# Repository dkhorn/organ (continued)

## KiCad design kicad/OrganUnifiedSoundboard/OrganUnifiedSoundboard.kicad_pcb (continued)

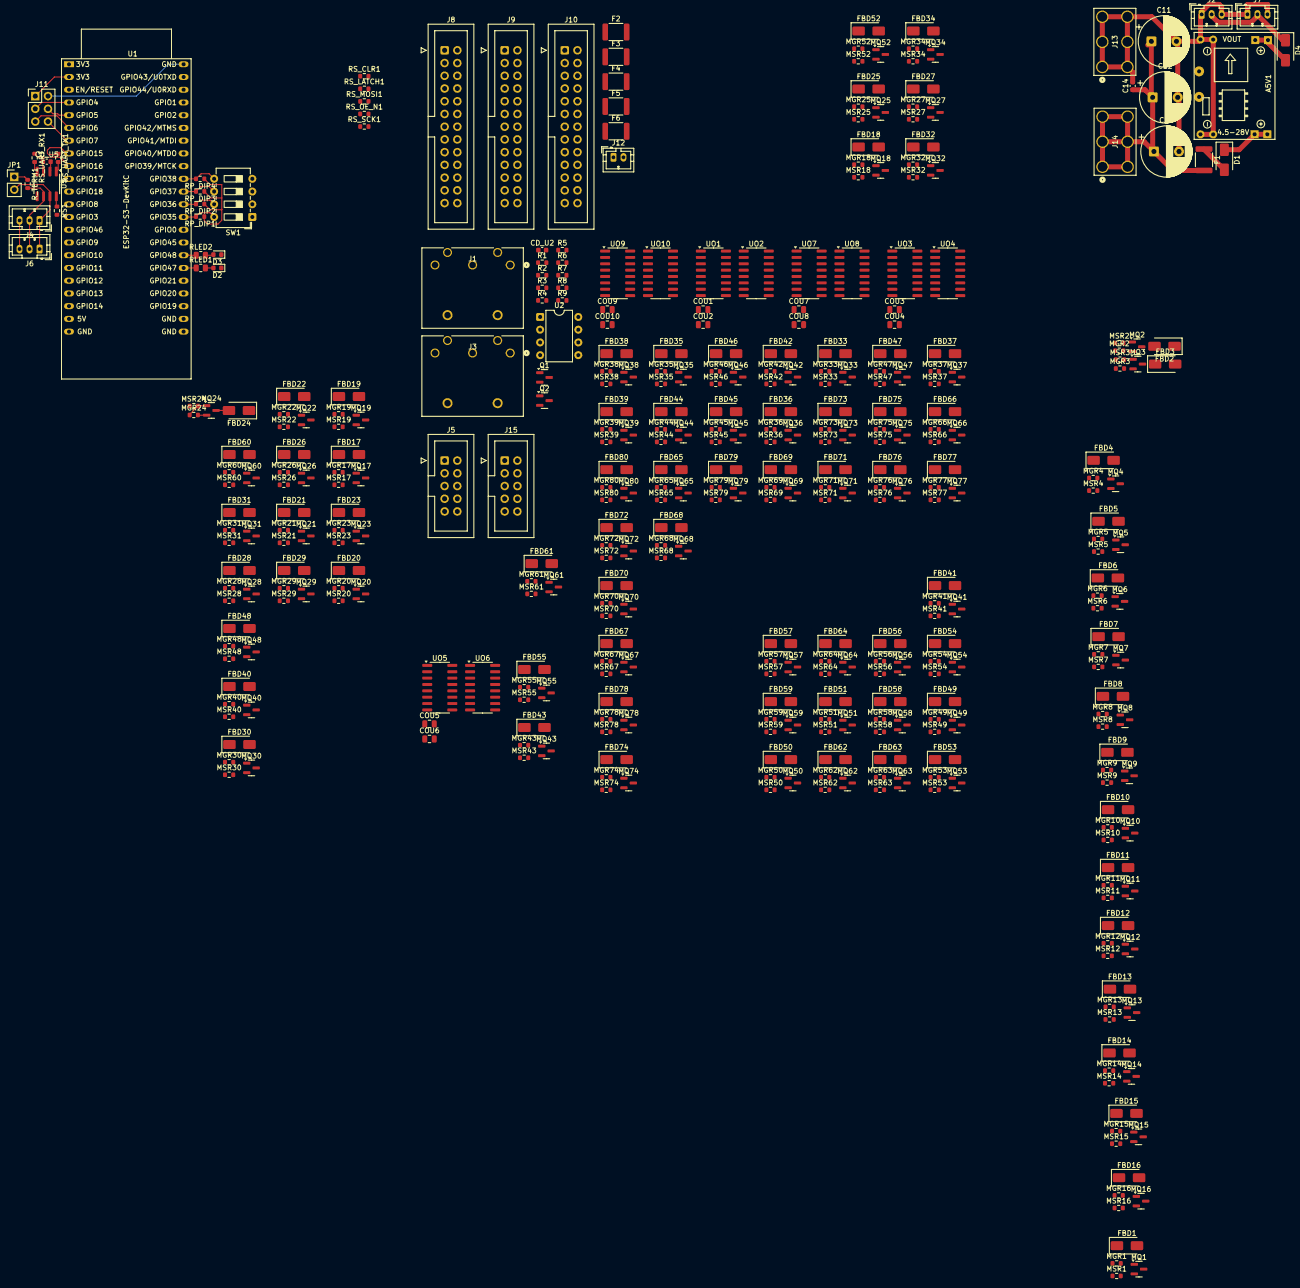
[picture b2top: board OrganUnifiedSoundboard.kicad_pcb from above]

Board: 2 copper layers, 403 parts (0 on the bottom side), 303 nets.

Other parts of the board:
J4: CAN_THRU; JST_PH_B3B-PH-K_1x03_P2.00mm_Vertical

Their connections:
/Controller/BoardToBoardComms/CANH: J4.1; also elsewhere on the board
/Controller/BoardToBoardComms/CANL: J4.2; also elsewhere on the board
GND: J4.3; also elsewhere on the board

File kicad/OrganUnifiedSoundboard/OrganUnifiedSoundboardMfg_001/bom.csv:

Designator,Footprint,Quantity,Value,LCSC Part #
"C11, C12, C13",CP_Radial_D10.0mm_P5.00mm,3,2200u 25V,
"C14, CD_U2, CD_U5",0603,3,100n,
"COU1, COU10, COU2, COU3, COU4, COU5, COU6, COU7, COU8, COU9",0805,10,0.1u,
CR1,SMCJSeries_LTF,1,SMCJ24A,
"D2, D3",0603,2,LED,
D4,D_SMA,1,SS14,
J10,IDC-Header_2x13_P2.54mm_Vertical,1,Outputs 53-78,
J8,IDC-Header_2x13_P2.54mm_Vertical,1,Outputs 1-26,
J9,IDC-Header_2x13_P2.54mm_Vertical,1,Outputs 27-52,
"MGR1, MGR10, MGR11, MGR12, MGR13, MGR14, MGR15, MGR16, MGR17, MGR18, MGR19, MGR2, MGR20, MGR21, MGR22, MGR23, MGR24, MGR25, MGR26, MGR27, MGR28, MGR29, MGR3, MGR30, MGR31, MGR32, MGR33, MGR34, MGR35, MGR36, MGR37, MGR38, MGR39, MGR4, MGR40, MGR41, MGR42, MGR43, MGR44, MGR45, MGR46, MGR47, MGR48, MGR49, MGR5, MGR50, MGR51, MGR52, MGR53, MGR54, MGR55, MGR56, MGR57, MGR58, MGR59, MGR6, MGR60, MGR61, MGR62, MGR63, MGR64, MGR65, MGR66, MGR67, MGR68, MGR69, MGR7, MGR70, MGR71, MGR72, MGR73, MGR74, MGR75, MGR76, MGR77, MGR78, MGR79, MGR8, MGR80, MGR9, R4, R9",0603,82,100K,
"MQ1, MQ10, MQ11, MQ12, MQ13, MQ14, MQ15, MQ16, MQ17, MQ18, MQ19, MQ2, MQ20, MQ21, MQ22, MQ23, MQ24, MQ25, MQ26, MQ27, MQ28, MQ29, MQ3, MQ30, MQ31, MQ32, MQ33, MQ34, MQ35, MQ36, MQ37, MQ38, MQ39, MQ4, MQ40, MQ41, MQ42, MQ43, MQ44, MQ45, MQ46, MQ47, MQ48, MQ49, MQ5, MQ50, MQ51, MQ52, MQ53, MQ54, MQ55, MQ56, MQ57, MQ58, MQ59, MQ6, MQ60, MQ61, MQ62, MQ63, MQ64, MQ65, MQ66, MQ67, MQ68, MQ69, MQ7, MQ70, MQ71, MQ72, MQ73, MQ74, MQ75, MQ76, MQ77, MQ78, MQ79, MQ8, MQ80, MQ9",SOT-23,80,Si2308CDS-T1-GE3,
"MSR1, MSR10, MSR11, MSR12, MSR13, MSR14, MSR15, MSR16, MSR17, MSR18, MSR19, MSR2, MSR20, MSR21, MSR22, MSR23, MSR24, MSR25, MSR26, MSR27, MSR28, MSR29, MSR3, MSR30, MSR31, MSR32, MSR33, MSR34, MSR35, MSR36, MSR37, MSR38, MSR39, MSR4, MSR40, MSR41, MSR42, MSR43, MSR44, MSR45, MSR46, MSR47, MSR48, MSR49, MSR5, MSR50, MSR51, MSR52, MSR53, MSR54, MSR55, MSR56, MSR57, MSR58, MSR59, MSR6, MSR60, MSR61, MSR62, MSR63, MSR64, MSR65, MSR66, MSR67, MSR68, MSR69, MSR7, MSR70, MSR71, MSR72, MSR73, MSR74, MSR75, MSR76, MSR77, MSR78, MSR79, MSR8, MSR80, MSR9",0603,80,100R,
"Q1, Q2",SOT-23,2,MMBT3904,
"R1, R8, RP_DIP1, RP_DIP2, RP_DIP3, RP_DIP4, RS1",0603,7,10k,
"R2, R5, R7",0603,3,220R,
R3,0603,1,2.2K,
R6,0603,1,4.7k,
"RLED1, RLED2",0805,2,4.7k,
"RS_UART_RX1, RS_UART_TX1",0603,2,33R,
R_TERM1,0603,1,120R,
U2,DIP-8_W7.62mm,1,6N137,
U5,SOIC-8_3.9x4.9mm_P1.27mm,1,SN65HVD230,
"UO1, UO10, UO2, UO3, UO4, UO5, UO6, UO7, UO8, UO9",SOP-16_3.9x9.9mm_P1.27mm,10,74HC595,

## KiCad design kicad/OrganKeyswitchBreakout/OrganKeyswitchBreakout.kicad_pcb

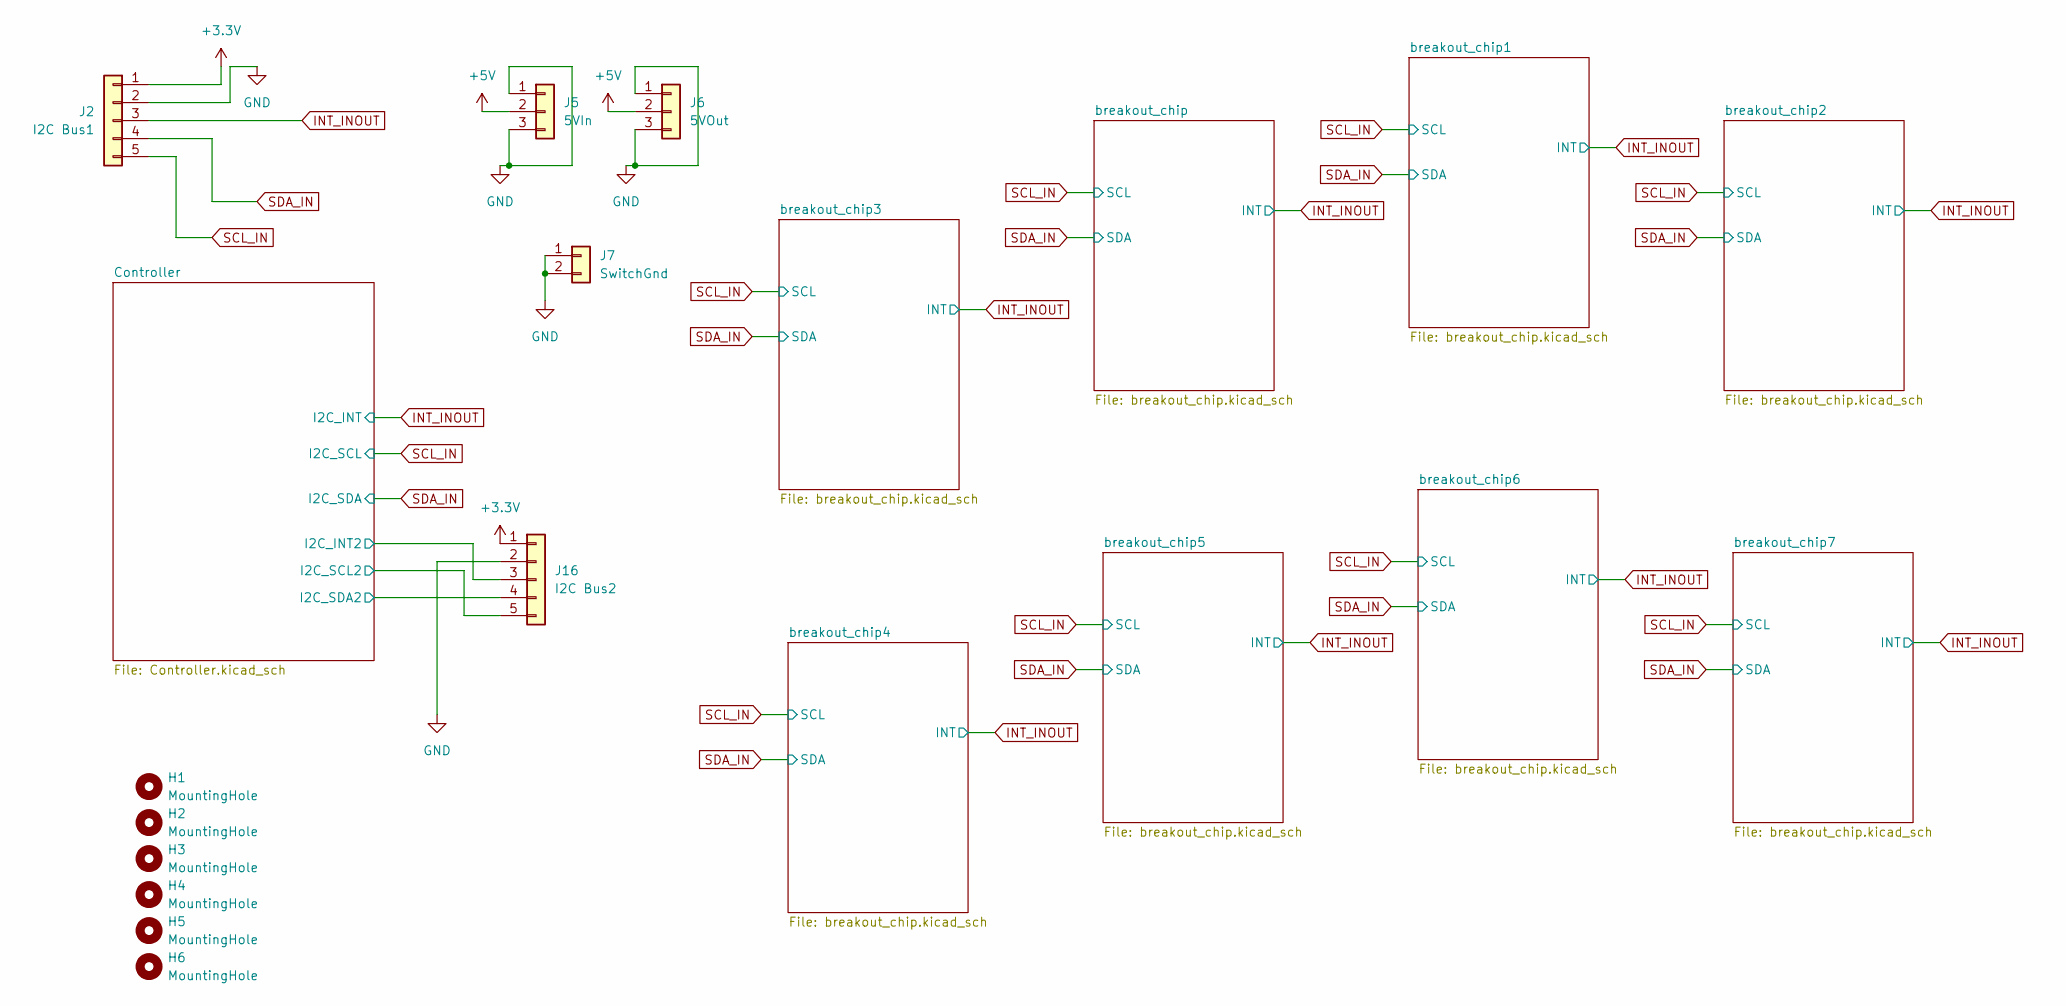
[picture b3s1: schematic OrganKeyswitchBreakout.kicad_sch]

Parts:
H1, H2, H3, H4, H5, H6: MountingHole; MountingHole_3.2mm_M3
J2: I2C Bus1; JST_PH_B5B-PH-K_1x05_P2.00mm_Vertical
J5: 5VIn; JST_PH_B3B-PH-K_1x03_P2.00mm_Vertical
J6: 5VOut; JST_PH_B3B-PH-K_1x03_P2.00mm_Vertical
J7: SwitchGnd; JST_PH_B2B-PH-K_1x02_P2.00mm_Vertical
J16: I2C Bus2; JST_PH_B5B-PH-K_1x05_P2.00mm_Vertical

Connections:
+3.3V: J2.1, J16.1; also elsewhere on the board
+5V: J5.2, J6.2; also elsewhere on the board
/Controller/I2C_INT2: J16.3; also elsewhere on the board
/Controller/I2C_SCL2: J16.5; also elsewhere on the board
/Controller/I2C_SDA2: J16.4; also elsewhere on the board
GND: J2.2, J5.1, J5.3, J6.1, J6.3, J7.1, J7.2, J16.2; also elsewhere on the board
INT_INOUT: J2.3; also elsewhere on the board
SCL_IN: J2.5; also elsewhere on the board
SDA_IN: J2.4; also elsewhere on the board

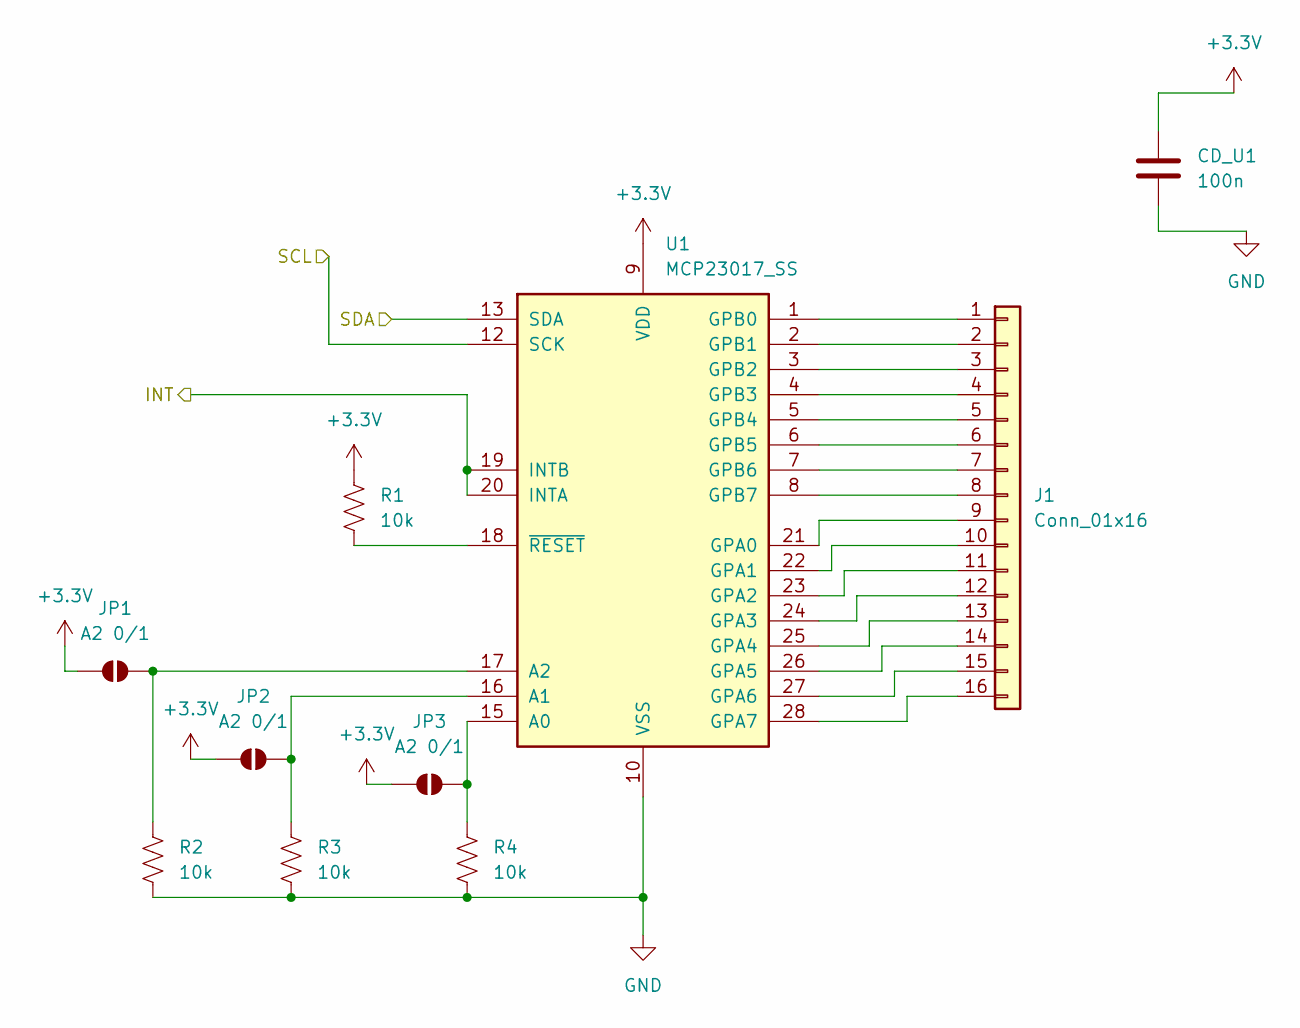
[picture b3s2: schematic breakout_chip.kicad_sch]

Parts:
CD_U1: 100n; C_0805_2012Metric
J1: Conn_01x16; IDC-Header_2x08_P2.54mm_Vertical
JP1, JP2, JP3: A2 0/1; SolderJumper-2_P1.3mm_Bridged_RoundedPad1.0x1.5mm
R1, R2, R3, R4: 10k; R_0805_2012Metric
U1: MCP23017_SS; SSOP-28_5.3x10.2mm_P0.65mm

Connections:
+3.3V: CD_U1.1, JP1.1 (A), JP2.1 (A), JP3.1 (A), R1.1, U1.9 (VDD); also elsewhere on the board
GND: CD_U1.2, R2.2, R3.2, R4.2, U1.10 (VSS); also elsewhere on the board
INT_INOUT: U1.19 (INTB), U1.20 (INTA); also elsewhere on the board
unnamed: J1.1, U1.1 (GPB0)
unnamed: J1.2, U1.2 (GPB1)
unnamed: J1.3, U1.3 (GPB2)
unnamed: J1.4, U1.4 (GPB3)
unnamed: J1.5, U1.5 (GPB4)
unnamed: J1.6, U1.6 (GPB5)
unnamed: J1.7, U1.7 (GPB6)
unnamed: J1.8, U1.8 (GPB7)
unnamed: J1.9, U1.21 (GPA0)
unnamed: J1.10, U1.22 (GPA1)
unnamed: J1.11, U1.23 (GPA2)
unnamed: J1.12, U1.24 (GPA3)
unnamed: J1.13, U1.25 (GPA4)
unnamed: J1.14, U1.26 (GPA5)
unnamed: J1.15, U1.27 (GPA6)
unnamed: J1.16, U1.28 (GPA7)
unnamed: JP1.2 (B), R2.1, U1.17 (A2)
unnamed: JP2.2 (B), R3.1, U1.16 (A1)
unnamed: JP3.2 (B), R4.1, U1.15 (A0)
unnamed: R1.2, U1.18 (~RESET)
SCL_IN: U1.12 (SCK); also elsewhere on the board
SDA_IN: U1.13 (SDA); also elsewhere on the board

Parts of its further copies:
CD_U3, CD_U4, CD_U5, CD_U6, CD_U7, CD_U8, CD_U9: 100n; C_0805_2012Metric
J8, J9, J10, J11, J12, J13, J14: Conn_01x16; IDC-Header_2x08_P2.54mm_Vertical
JP4, JP5, JP6, JP7, JP8, JP9, JP10, JP11, JP12, JP13, JP14, JP15, JP16, JP17, JP18, JP19, JP20, JP21, JP22, JP23, JP24: A2 0/1; SolderJumper-2_P1.3mm_Bridged_RoundedPad1.0x1.5mm
R12, R13, R14, R15, R16, R17, R18, R19, R20, R21, R22, R23, R24, R25, R26, R27, R28, R29, R30, R31, R32, R33, R34, R35, R36, R37, R38, R39: 10k; R_0805_2012Metric
U4, U5, U6, U7, U8, U9, U10: MCP23017_SS; SSOP-28_5.3x10.2mm_P0.65mm

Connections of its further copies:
+3.3V: CD_U3.1, CD_U4.1, CD_U5.1, CD_U6.1, CD_U7.1, CD_U8.1, CD_U9.1, JP4.1 (A), JP5.1 (A), JP6.1 (A), JP7.1 (A), JP8.1 (A), JP9.1 (A), JP10.1 (A), JP11.1 (A), JP12.1 (A), JP13.1 (A), JP14.1 (A), JP15.1 (A), JP16.1 (A), JP17.1 (A), JP18.1 (A), JP19.1 (A), JP20.1 (A), JP21.1 (A), JP22.1 (A), JP23.1 (A), JP24.1 (A), R12.1, R16.1, R20.1, R24.1, R28.1, R32.1, R36.1, U4.9 (VDD), U5.9 (VDD), U6.9 (VDD), U7.9 (VDD), U8.9 (VDD), U9.9 (VDD), U10.9 (VDD); also elsewhere on the board
GND: CD_U3.2, CD_U4.2, CD_U5.2, CD_U6.2, CD_U7.2, CD_U8.2, CD_U9.2, R13.2, R14.2, R15.2, R17.2, R18.2, R19.2, R21.2, R22.2, R23.2, R25.2, R26.2, R27.2, R29.2, R30.2, R31.2, R33.2, R34.2, R35.2, R37.2, R38.2, R39.2, U4.10 (VSS), U5.10 (VSS), U6.10 (VSS), U7.10 (VSS), U8.10 (VSS), U9.10 (VSS), U10.10 (VSS); also elsewhere on the board
INT_INOUT: U4.19 (INTB), U4.20 (INTA), U5.19 (INTB), U5.20 (INTA), U6.19 (INTB), U6.20 (INTA), U7.19 (INTB), U7.20 (INTA), U8.19 (INTB), U8.20 (INTA), U9.19 (INTB), U9.20 (INTA), U10.19 (INTB), U10.20 (INTA); also elsewhere on the board
unnamed: J8.1, U4.1 (GPB0)
unnamed: J8.2, U4.2 (GPB1)
unnamed: J8.3, U4.3 (GPB2)
unnamed: J8.4, U4.4 (GPB3)
unnamed: J8.5, U4.5 (GPB4)
unnamed: J8.6, U4.6 (GPB5)
unnamed: J8.7, U4.7 (GPB6)
unnamed: J8.8, U4.8 (GPB7)
unnamed: J8.9, U4.21 (GPA0)
unnamed: J8.10, U4.22 (GPA1)
unnamed: J8.11, U4.23 (GPA2)
unnamed: J8.12, U4.24 (GPA3)
unnamed: J8.13, U4.25 (GPA4)
unnamed: J8.14, U4.26 (GPA5)
unnamed: J8.15, U4.27 (GPA6)
unnamed: J8.16, U4.28 (GPA7)
unnamed: J9.1, U5.1 (GPB0)
unnamed: J9.2, U5.2 (GPB1)
unnamed: J9.3, U5.3 (GPB2)
unnamed: J9.4, U5.4 (GPB3)
unnamed: J9.5, U5.5 (GPB4)
unnamed: J9.6, U5.6 (GPB5)
unnamed: J9.7, U5.7 (GPB6)
unnamed: J9.8, U5.8 (GPB7)
unnamed: J9.9, U5.21 (GPA0)
unnamed: J9.10, U5.22 (GPA1)
unnamed: J9.11, U5.23 (GPA2)
unnamed: J9.12, U5.24 (GPA3)
unnamed: J9.13, U5.25 (GPA4)
unnamed: J9.14, U5.26 (GPA5)
unnamed: J9.15, U5.27 (GPA6)
unnamed: J9.16, U5.28 (GPA7)
unnamed: J10.1, U6.1 (GPB0)
unnamed: J10.2, U6.2 (GPB1)
unnamed: J10.3, U6.3 (GPB2)
unnamed: J10.4, U6.4 (GPB3)
unnamed: J10.5, U6.5 (GPB4)
unnamed: J10.6, U6.6 (GPB5)
unnamed: J10.7, U6.7 (GPB6)
unnamed: J10.8, U6.8 (GPB7)
unnamed: J10.9, U6.21 (GPA0)
unnamed: J10.10, U6.22 (GPA1)
unnamed: J10.11, U6.23 (GPA2)
unnamed: J10.12, U6.24 (GPA3)
unnamed: J10.13, U6.25 (GPA4)
unnamed: J10.14, U6.26 (GPA5)
unnamed: J10.15, U6.27 (GPA6)
unnamed: J10.16, U6.28 (GPA7)
unnamed: J11.1, U7.1 (GPB0)
unnamed: J11.2, U7.2 (GPB1)
unnamed: J11.3, U7.3 (GPB2)
unnamed: J11.4, U7.4 (GPB3)
unnamed: J11.5, U7.5 (GPB4)
unnamed: J11.6, U7.6 (GPB5)
unnamed: J11.7, U7.7 (GPB6)
unnamed: J11.8, U7.8 (GPB7)
unnamed: J11.9, U7.21 (GPA0)
unnamed: J11.10, U7.22 (GPA1)
unnamed: J11.11, U7.23 (GPA2)
unnamed: J11.12, U7.24 (GPA3)
unnamed: J11.13, U7.25 (GPA4)
unnamed: J11.14, U7.26 (GPA5)
unnamed: J11.15, U7.27 (GPA6)
unnamed: J11.16, U7.28 (GPA7)
unnamed: J12.1, U8.1 (GPB0)
unnamed: J12.2, U8.2 (GPB1)
unnamed: J12.3, U8.3 (GPB2)
unnamed: J12.4, U8.4 (GPB3)
unnamed: J12.5, U8.5 (GPB4)
unnamed: J12.6, U8.6 (GPB5)
unnamed: J12.7, U8.7 (GPB6)
unnamed: J12.8, U8.8 (GPB7)
unnamed: J12.9, U8.21 (GPA0)
unnamed: J12.10, U8.22 (GPA1)
unnamed: J12.11, U8.23 (GPA2)
unnamed: J12.12, U8.24 (GPA3)
unnamed: J12.13, U8.25 (GPA4)
unnamed: J12.14, U8.26 (GPA5)
unnamed: J12.15, U8.27 (GPA6)
unnamed: J12.16, U8.28 (GPA7)
unnamed: J13.1, U9.1 (GPB0)
unnamed: J13.2, U9.2 (GPB1)
unnamed: J13.3, U9.3 (GPB2)
unnamed: J13.4, U9.4 (GPB3)
unnamed: J13.5, U9.5 (GPB4)
unnamed: J13.6, U9.6 (GPB5)
unnamed: J13.7, U9.7 (GPB6)
unnamed: J13.8, U9.8 (GPB7)
unnamed: J13.9, U9.21 (GPA0)
unnamed: J13.10, U9.22 (GPA1)
unnamed: J13.11, U9.23 (GPA2)
unnamed: J13.12, U9.24 (GPA3)
unnamed: J13.13, U9.25 (GPA4)
unnamed: J13.14, U9.26 (GPA5)
unnamed: J13.15, U9.27 (GPA6)
unnamed: J13.16, U9.28 (GPA7)
unnamed: J14.1, U10.1 (GPB0)
unnamed: J14.2, U10.2 (GPB1)
unnamed: J14.3, U10.3 (GPB2)
unnamed: J14.4, U10.4 (GPB3)
unnamed: J14.5, U10.5 (GPB4)
unnamed: J14.6, U10.6 (GPB5)
unnamed: J14.7, U10.7 (GPB6)
unnamed: J14.8, U10.8 (GPB7)
unnamed: J14.9, U10.21 (GPA0)
unnamed: J14.10, U10.22 (GPA1)
unnamed: J14.11, U10.23 (GPA2)
unnamed: J14.12, U10.24 (GPA3)
unnamed: J14.13, U10.25 (GPA4)
unnamed: J14.14, U10.26 (GPA5)
unnamed: J14.15, U10.27 (GPA6)
unnamed: J14.16, U10.28 (GPA7)
unnamed: JP4.2 (B), R13.1, U4.17 (A2)
unnamed: JP5.2 (B), R14.1, U4.16 (A1)
unnamed: JP6.2 (B), R15.1, U4.15 (A0)
unnamed: JP7.2 (B), R17.1, U5.17 (A2)
unnamed: JP8.2 (B), R18.1, U5.16 (A1)
unnamed: JP9.2 (B), R19.1, U5.15 (A0)
unnamed: JP10.2 (B), R21.1, U6.17 (A2)
unnamed: JP11.2 (B), R22.1, U6.16 (A1)
unnamed: JP12.2 (B), R23.1, U6.15 (A0)
unnamed: JP13.2 (B), R25.1, U7.17 (A2)
unnamed: JP14.2 (B), R26.1, U7.16 (A1)
unnamed: JP15.2 (B), R27.1, U7.15 (A0)
unnamed: JP16.2 (B), R29.1, U8.17 (A2)
unnamed: JP17.2 (B), R30.1, U8.16 (A1)
unnamed: JP18.2 (B), R31.1, U8.15 (A0)
unnamed: JP19.2 (B), R33.1, U9.17 (A2)
unnamed: JP20.2 (B), R34.1, U9.16 (A1)
unnamed: JP21.2 (B), R35.1, U9.15 (A0)
unnamed: JP22.2 (B), R37.1, U10.17 (A2)
unnamed: JP23.2 (B), R38.1, U10.16 (A1)
unnamed: JP24.2 (B), R39.1, U10.15 (A0)
unnamed: R12.2, U4.18 (~RESET)
unnamed: R16.2, U5.18 (~RESET)
unnamed: R20.2, U6.18 (~RESET)
unnamed: R24.2, U7.18 (~RESET)
unnamed: R28.2, U8.18 (~RESET)
unnamed: R32.2, U9.18 (~RESET)
unnamed: R36.2, U10.18 (~RESET)
SCL_IN: U4.12 (SCK), U5.12 (SCK), U6.12 (SCK), U7.12 (SCK), U8.12 (SCK), U9.12 (SCK), U10.12 (SCK); also elsewhere on the board
SDA_IN: U4.13 (SDA), U5.13 (SDA), U6.13 (SDA), U7.13 (SDA), U8.13 (SDA), U9.13 (SDA), U10.13 (SDA); also elsewhere on the board

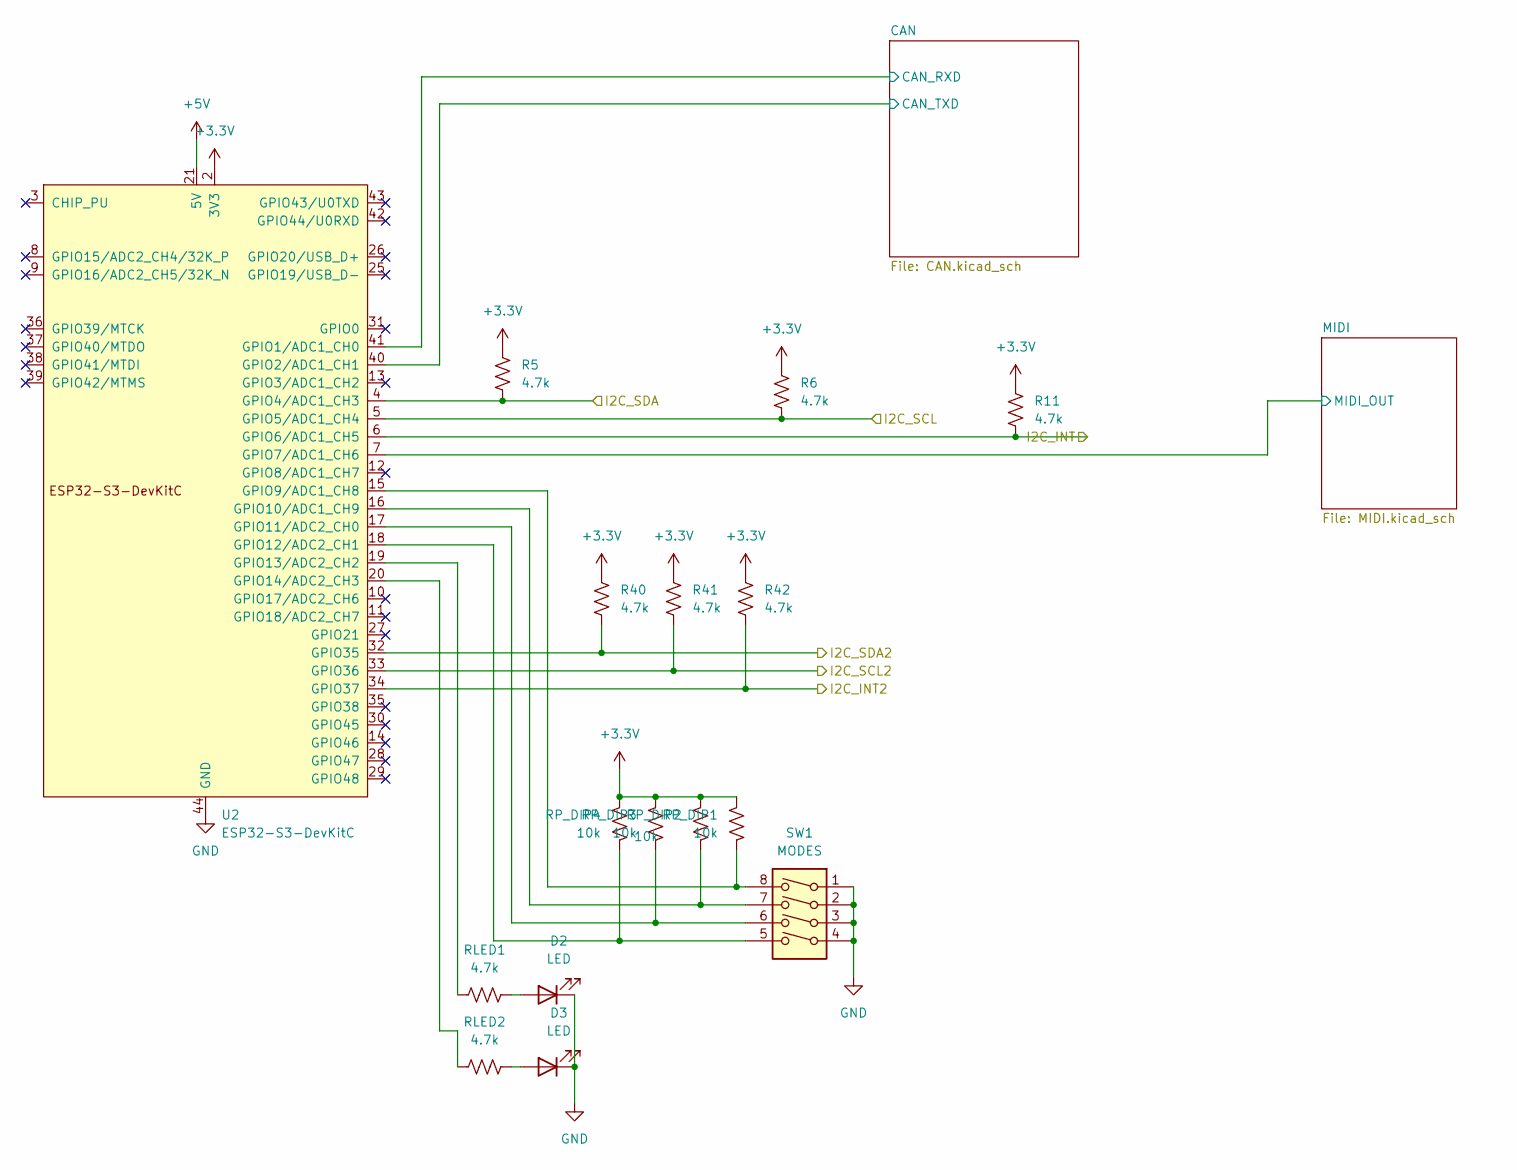
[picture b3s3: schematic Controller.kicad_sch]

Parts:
D2, D3: LED; LED_0603_1608Metric
R5, R6, R11, R40, R41, R42: 4.7k; R_0805_2012Metric
RLED1, RLED2: 4.7k; R_0805_2012Metric
RP_DIP1, RP_DIP2, RP_DIP3, RP_DIP4: 10k; R_0603_1608Metric
SW1: MODES; SW_DIP_SPSTx04_Slide_6.7x11.72mm_W7.62mm_P2.54mm_LowProfile
U2: ESP32-S3-DevKitC

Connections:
+3.3V: R5.1, R6.1, R11.1, R40.1, R41.1, R42.1, RP_DIP1.1, RP_DIP2.1, RP_DIP3.1, RP_DIP4.1, U2.1 (3V3), U2.2 (3V3); also elsewhere on the board
+5V: U2.21 (5V); also elsewhere on the board
/Controller/CAN/CAN_RXD: U2.41 (GPIO1/ADC1_CH0); also elsewhere on the board
/Controller/CAN/CAN_TXD: U2.40 (GPIO2/ADC1_CH1); also elsewhere on the board
/Controller/I2C_INT2: R42.2, U2.34 (GPIO37); also elsewhere on the board
/Controller/I2C_SCL2: R41.2, U2.33 (GPIO36); also elsewhere on the board
/Controller/I2C_SDA2: R40.2, U2.32 (GPIO35); also elsewhere on the board
/Controller/MIDI/MIDI_OUT: U2.7 (GPIO7/ADC1_CH6); also elsewhere on the board
GND: D2.1 (K), D3.1 (K), SW1.1, SW1.2, SW1.3, SW1.4, U2.22 (GND), U2.23 (GND), U2.24 (GND), U2.44 (GND); also elsewhere on the board
INT_INOUT: R11.2, U2.6 (GPIO6/ADC1_CH5); also elsewhere on the board
unnamed: D2.2 (A), RLED1.2
unnamed: D3.2 (A), RLED2.2
unnamed: RP_DIP1.2, SW1.8, U2.15 (GPIO9/ADC1_CH8)
unnamed: RP_DIP2.2, SW1.7, U2.16 (GPIO10/ADC1_CH9)
unnamed: RP_DIP3.2, SW1.6, U2.17 (GPIO11/ADC2_CH0)
unnamed: RP_DIP4.2, SW1.5, U2.18 (GPIO12/ADC2_CH1)
unnamed: RLED1.1, U2.19 (GPIO13/ADC2_CH2)
unnamed: RLED2.1, U2.20 (GPIO14/ADC2_CH3)
SCL_IN: R6.2, U2.5 (GPIO5/ADC1_CH4); also elsewhere on the board
SDA_IN: R5.2, U2.4 (GPIO4/ADC1_CH3); also elsewhere on the board

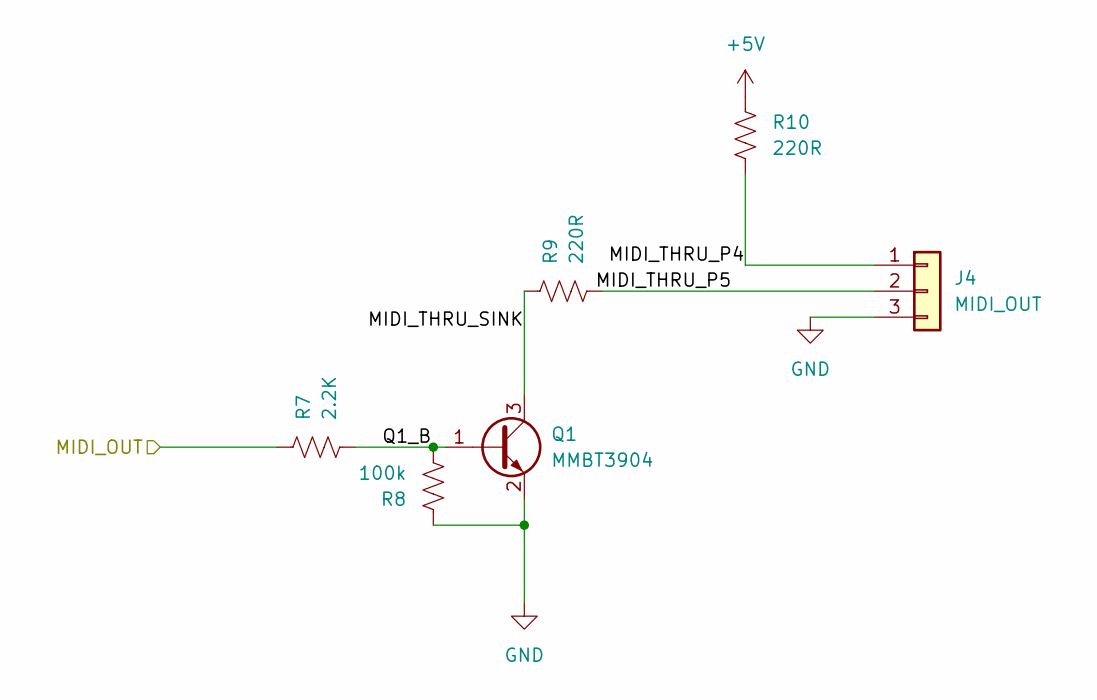
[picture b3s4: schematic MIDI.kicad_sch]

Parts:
J4: MIDI_OUT; JST_PH_B3B-PH-K_1x03_P2.00mm_Vertical
Q1: MMBT3904; SOT-23
R7: 2.2K; R_0603_1608Metric
R8: 100k; R_0603_1608Metric
R9, R10: 220R; R_0603_1608Metric

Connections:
+5V: R10.1; also elsewhere on the board
/Controller/MIDI/MIDI_OUT: R7.1; also elsewhere on the board
/Controller/MIDI/MIDI_THRU_P4: J4.1, R10.2
/Controller/MIDI/MIDI_THRU_P5: J4.2, R9.2
/Controller/MIDI/MIDI_THRU_SINK: Q1.3 (C), R9.1
/Controller/MIDI/Q1_B: Q1.1 (B), R7.2, R8.2
GND: J4.3, Q1.2 (E), R8.1; also elsewhere on the board

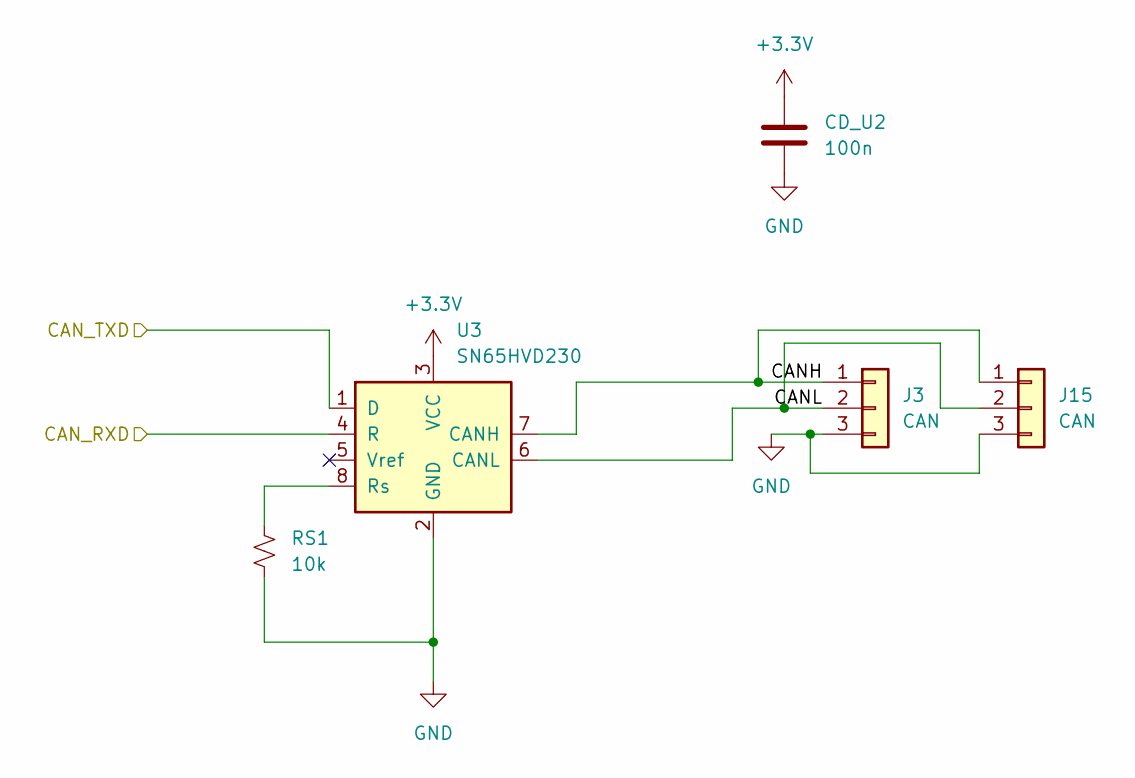
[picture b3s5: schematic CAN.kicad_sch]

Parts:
CD_U2: 100n; C_0603_1608Metric
J3, J15: CAN; JST_PH_B3B-PH-K_1x03_P2.00mm_Vertical
RS1: 10k; R_0603_1608Metric
U3: SN65HVD230; SOIC-8_3.9x4.9mm_P1.27mm

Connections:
+3.3V: CD_U2.1, U3.3 (VCC); also elsewhere on the board
/Controller/CAN/CANH: J3.1, J15.1, U3.7 (CANH)
/Controller/CAN/CANL: J3.2, J15.2, U3.6 (CANL)
/Controller/CAN/CAN_RXD: U3.4 (R); also elsewhere on the board
/Controller/CAN/CAN_TXD: U3.1 (D); also elsewhere on the board
GND: CD_U2.2, J3.3, J15.3, RS1.2, U3.2 (GND); also elsewhere on the board
unnamed: RS1.1, U3.8 (Rs)

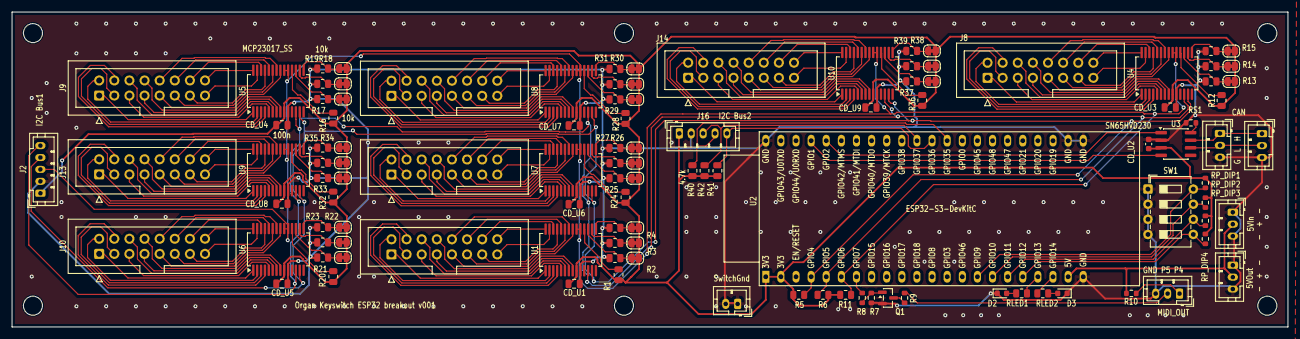
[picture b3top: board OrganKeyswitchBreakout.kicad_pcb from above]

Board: 2 copper layers, 214.4 x 52.9 mm, 118 parts (0 on the bottom side), 187 nets.

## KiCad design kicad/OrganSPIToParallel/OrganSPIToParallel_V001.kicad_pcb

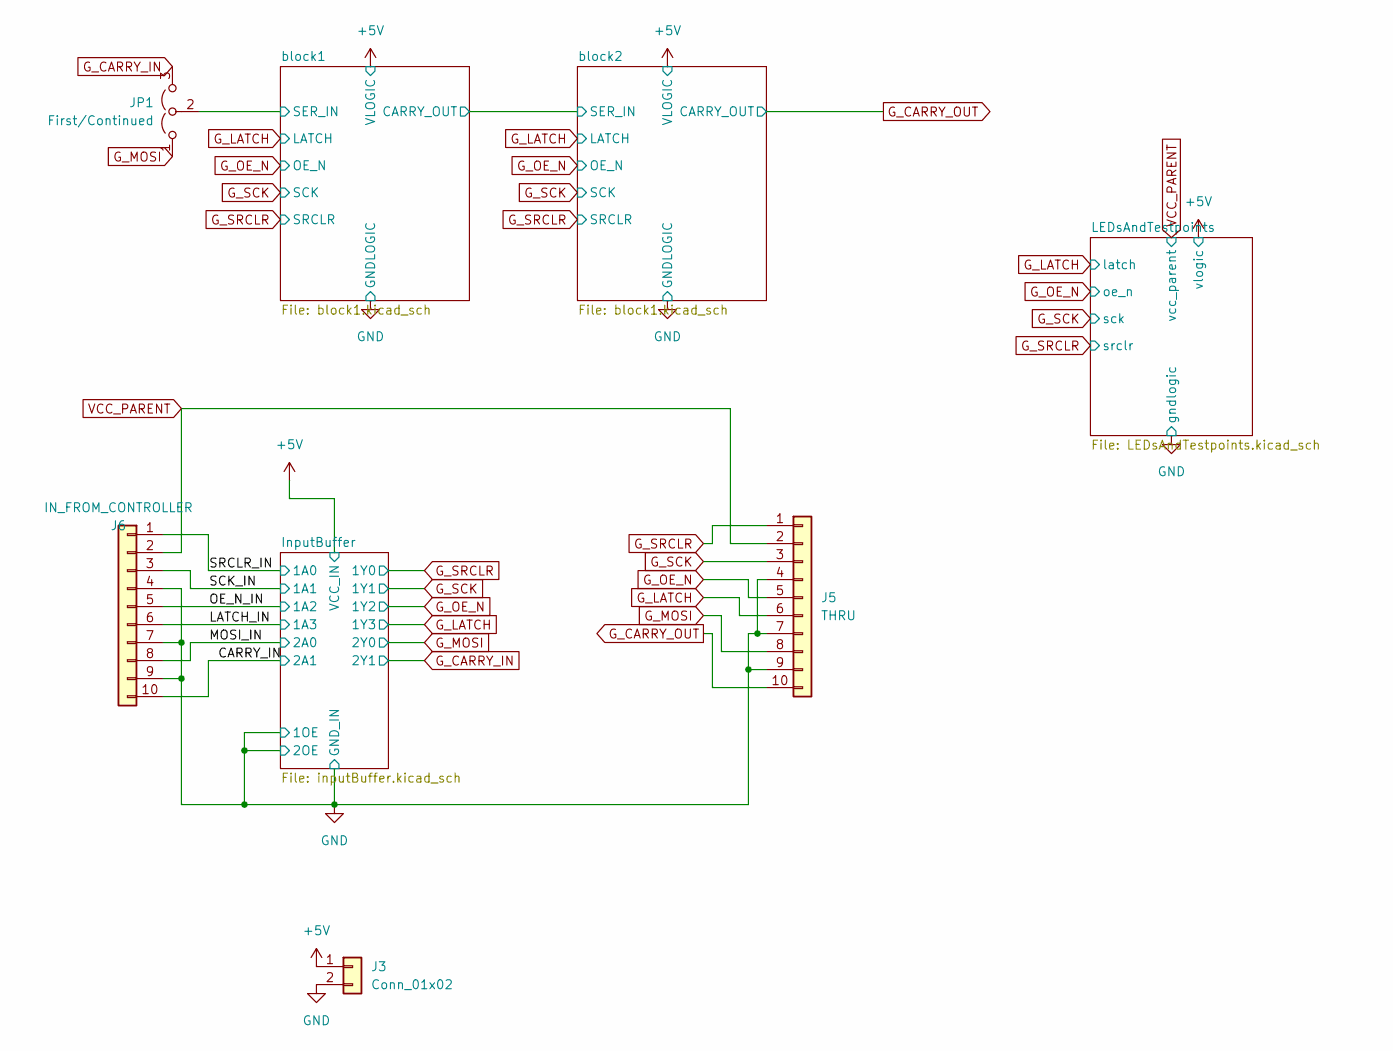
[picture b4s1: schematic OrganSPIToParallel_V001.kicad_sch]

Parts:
J3: Conn_01x02; JST_PH_B2B-PH-K_1x02_P2.00mm_Vertical
J5: THRU; IDC-Header_2x05_P2.54mm_Vertical
J6: IN_FROM_CONTROLLER; IDC-Header_2x05_P2.54mm_Vertical
JP1: First/Continued; PinHeader_1x03_P2.54mm_Vertical

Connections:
+5V: J3.1; also elsewhere on the board
/CARRY_IN: J6.10; also elsewhere on the board
/LATCH_IN: J6.6; also elsewhere on the board
/MOSI_IN: J6.8; also elsewhere on the board
/OE_N_IN: J6.5; also elsewhere on the board
/SCK_IN: J6.3; also elsewhere on the board
/SRCLR_IN: J6.1; also elsewhere on the board
/block1/SER_IN: JP1.2 (C); also elsewhere on the board
GND: J3.2, J5.4, J5.7, J5.9, J6.4, J6.7, J6.9; also elsewhere on the board
G_CARRY_IN: JP1.3 (B); also elsewhere on the board
G_CARRY_OUT: J5.10; also elsewhere on the board
G_LATCH: J5.6; also elsewhere on the board
G_MOSI: J5.8, JP1.1 (A); also elsewhere on the board
G_OE_N: J5.5; also elsewhere on the board
G_SCK: J5.3; also elsewhere on the board
G_SRCLR: J5.1; also elsewhere on the board
VCC_PARENT: J5.2, J6.2; also elsewhere on the board

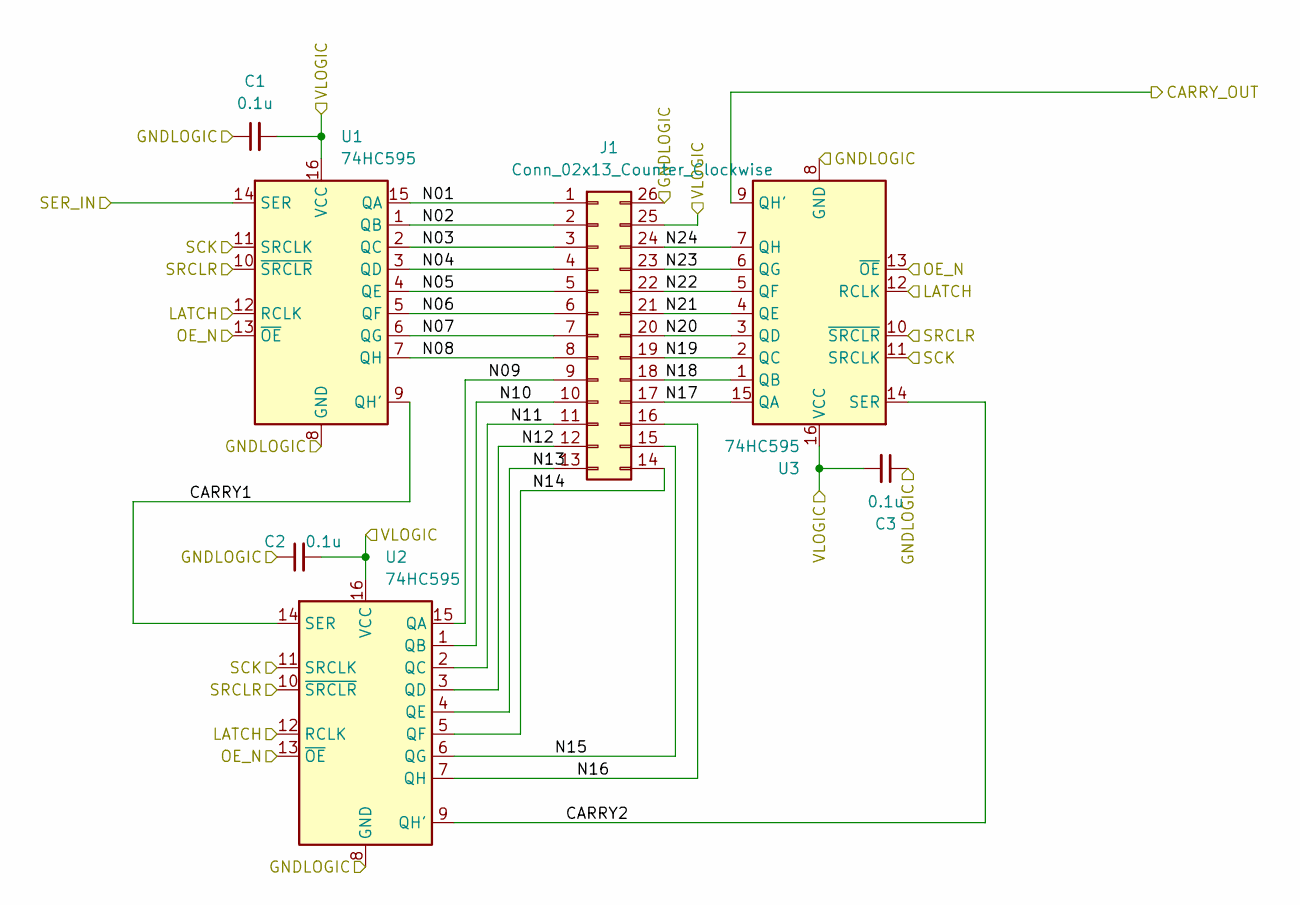
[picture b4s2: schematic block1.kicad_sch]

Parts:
C1, C2, C3: 0.1u; C_0805_2012Metric
J1: Conn_02x13_Counter_Clockwise; IDC-Header_2x13_P2.54mm_Vertical
U1, U2, U3: 74HC595; SOP-16_3.9x9.9mm_P1.27mm

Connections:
+5V: C1.2, C2.2, C3.2, J1.25, U1.16 (VCC), U2.16 (VCC), U3.16 (VCC); also elsewhere on the board
/block1/CARRY1: U1.9 (QH'), U2.14 (SER)
/block1/CARRY2: U2.9 (QH'), U3.14 (SER)
/block1/CARRY_OUT: U3.9 (QH'); also elsewhere on the board
/block1/N01: J1.1, U1.15 (QA)
/block1/N02: J1.2, U1.1 (QB)
/block1/N03: J1.3, U1.2 (QC)
/block1/N04: J1.4, U1.3 (QD)
/block1/N05: J1.5, U1.4 (QE)
/block1/N06: J1.6, U1.5 (QF)
/block1/N07: J1.7, U1.6 (QG)
/block1/N08: J1.8, U1.7 (QH)
/block1/N09: J1.9, U2.15 (QA)
/block1/N10: J1.10, U2.1 (QB)
/block1/N11: J1.11, U2.2 (QC)
/block1/N12: J1.12, U2.3 (QD)
/block1/N13: J1.13, U2.4 (QE)
/block1/N14: J1.14, U2.5 (QF)
/block1/N15: J1.15, U2.6 (QG)
/block1/N16: J1.16, U2.7 (QH)
/block1/N17: J1.17, U3.15 (QA)
/block1/N18: J1.18, U3.1 (QB)
/block1/N19: J1.19, U3.2 (QC)
/block1/N20: J1.20, U3.3 (QD)
/block1/N21: J1.21, U3.4 (QE)
/block1/N22: J1.22, U3.5 (QF)
/block1/N23: J1.23, U3.6 (QG)
/block1/N24: J1.24, U3.7 (QH)
/block1/SER_IN: U1.14 (SER); also elsewhere on the board
GND: C1.1, C2.1, C3.1, J1.26, U1.8 (GND), U2.8 (GND), U3.8 (GND); also elsewhere on the board
G_LATCH: U1.12 (RCLK), U2.12 (RCLK), U3.12 (RCLK); also elsewhere on the board
G_OE_N: U1.13 (~OE), U2.13 (~OE), U3.13 (~OE); also elsewhere on the board
G_SCK: U1.11 (SRCLK), U2.11 (SRCLK), U3.11 (SRCLK); also elsewhere on the board
G_SRCLR: U1.10 (~SRCLR), U2.10 (~SRCLR), U3.10 (~SRCLR); also elsewhere on the board

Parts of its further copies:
C4, C5, C6: 0.1u; C_0805_2012Metric
J2: Conn_02x13_Counter_Clockwise; IDC-Header_2x13_P2.54mm_Vertical
U4, U5, U6: 74HC595; SOP-16_3.9x9.9mm_P1.27mm

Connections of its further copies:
+5V: C4.2, C5.2, C6.2, J2.25, U4.16 (VCC), U5.16 (VCC), U6.16 (VCC); also elsewhere on the board
/block1/CARRY_OUT: U4.14 (SER); also elsewhere on the board
/block2/CARRY1: U4.9 (QH'), U5.14 (SER)
/block2/CARRY2: U5.9 (QH'), U6.14 (SER)
/block2/N01: J2.1, U4.15 (QA)
/block2/N02: J2.2, U4.1 (QB)
/block2/N03: J2.3, U4.2 (QC)
/block2/N04: J2.4, U4.3 (QD)
/block2/N05: J2.5, U4.4 (QE)
/block2/N06: J2.6, U4.5 (QF)
/block2/N07: J2.7, U4.6 (QG)
/block2/N08: J2.8, U4.7 (QH)
/block2/N09: J2.9, U5.15 (QA)
/block2/N10: J2.10, U5.1 (QB)
/block2/N11: J2.11, U5.2 (QC)
/block2/N12: J2.12, U5.3 (QD)
/block2/N13: J2.13, U5.4 (QE)
/block2/N14: J2.14, U5.5 (QF)
/block2/N15: J2.15, U5.6 (QG)
/block2/N16: J2.16, U5.7 (QH)
/block2/N17: J2.17, U6.15 (QA)
/block2/N18: J2.18, U6.1 (QB)
/block2/N19: J2.19, U6.2 (QC)
/block2/N20: J2.20, U6.3 (QD)
/block2/N21: J2.21, U6.4 (QE)
/block2/N22: J2.22, U6.5 (QF)
/block2/N23: J2.23, U6.6 (QG)
/block2/N24: J2.24, U6.7 (QH)
GND: C4.1, C5.1, C6.1, J2.26, U4.8 (GND), U5.8 (GND), U6.8 (GND); also elsewhere on the board
G_CARRY_OUT: U6.9 (QH'); also elsewhere on the board
G_LATCH: U4.12 (RCLK), U5.12 (RCLK), U6.12 (RCLK); also elsewhere on the board
G_OE_N: U4.13 (~OE), U5.13 (~OE), U6.13 (~OE); also elsewhere on the board
G_SCK: U4.11 (SRCLK), U5.11 (SRCLK), U6.11 (SRCLK); also elsewhere on the board
G_SRCLR: U4.10 (~SRCLR), U5.10 (~SRCLR), U6.10 (~SRCLR); also elsewhere on the board
